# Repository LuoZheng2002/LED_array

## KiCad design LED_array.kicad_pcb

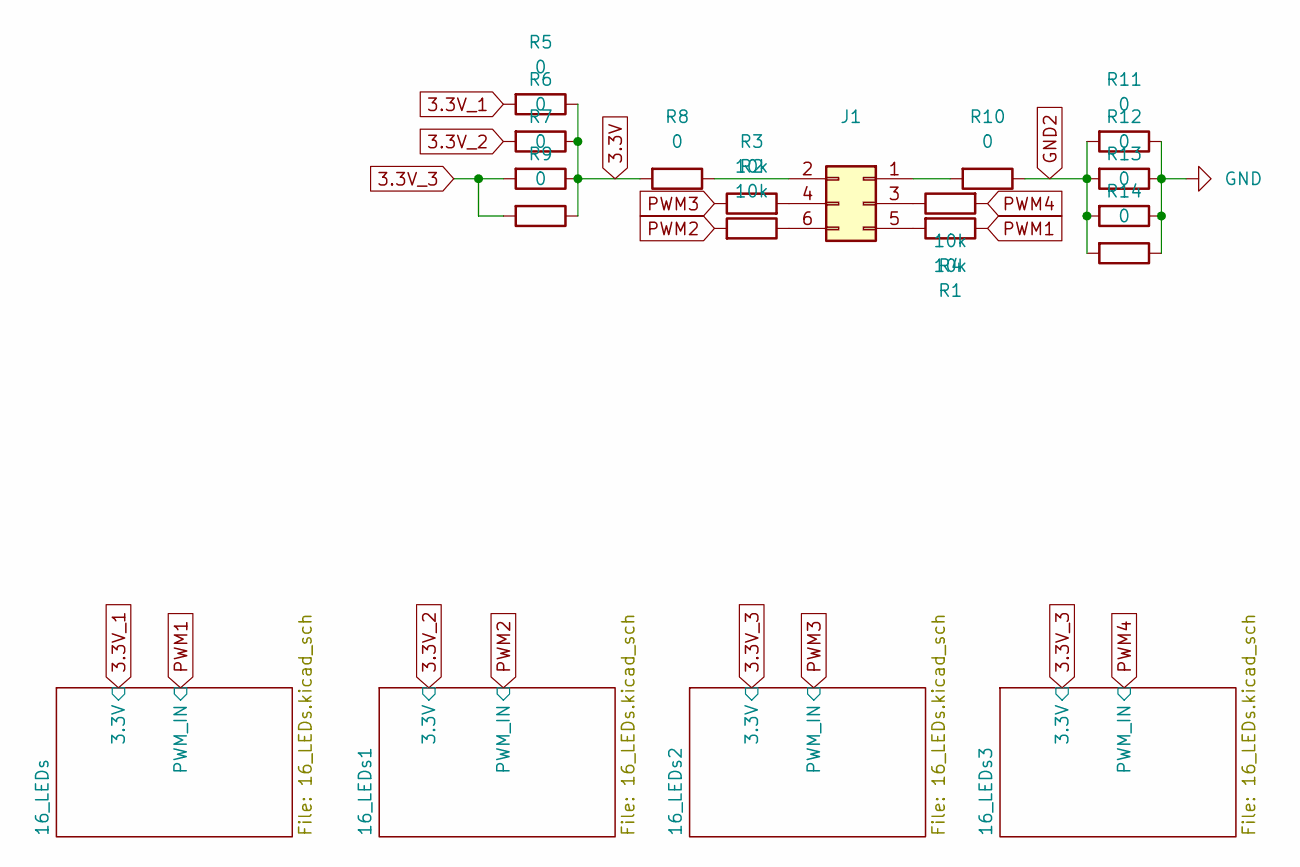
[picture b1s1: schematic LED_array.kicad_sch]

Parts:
J1: Conn_02x03_Odd_Even; PinSocket_2x03_P2.54mm_Vertical
R1, R2, R3, R4: 10k; R_Axial_DIN0207_L6.3mm_D2.5mm_P7.62mm_Horizontal
R5, R6, R11: 0; R_Axial_DIN0204_L3.6mm_D1.6mm_P5.08mm_Horizontal
R7, R8, R9, R12: 0; R_Axial_DIN0204_L3.6mm_D1.6mm_P7.62mm_Horizontal
R10, R13, R14: 0; my10.16mm_resistor

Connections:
3.3V: R5.1, R6.1, R7.1, R8.2, R9.1
3.3V_1: R5.2; also elsewhere on the board
3.3V_2: R6.2; also elsewhere on the board
3.3V_3: R7.2, R9.2; also elsewhere on the board
GND: R11.1, R12.1, R13.1, R14.1; also elsewhere on the board
GND2: R10.1, R11.2, R12.2, R13.2, R14.2
unnamed: J1.1, R10.2
unnamed: J1.2, R8.1
unnamed: J1.3, R4.1
unnamed: J1.4, R3.2
unnamed: J1.5, R1.2
unnamed: J1.6, R2.1
PWM1: R1.1; also elsewhere on the board
PWM2: R2.2; also elsewhere on the board
PWM3: R3.1; also elsewhere on the board
PWM4: R4.2; also elsewhere on the board

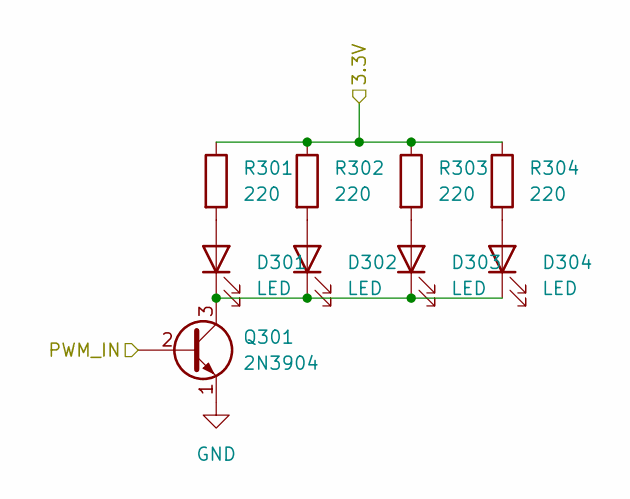
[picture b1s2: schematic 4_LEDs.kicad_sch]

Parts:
D301, D302, D303, D304: LED; LED_D5.0mm
Q301: 2N3904; TO-92_Inline
R301, R302, R303, R304: 220; R_Axial_DIN0207_L6.3mm_D2.5mm_P7.62mm_Horizontal

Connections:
3.3V_1: R301.1, R302.1, R303.1, R304.1; also elsewhere on the board
GND: Q301.1 (E); also elsewhere on the board
unnamed: D301.2 (A), R301.2
unnamed: D301.1 (K), D302.1 (K), D303.1 (K), D304.1 (K), Q301.3 (C)
unnamed: D302.2 (A), R302.2
unnamed: D303.2 (A), R303.2
unnamed: D304.2 (A), R304.2
PWM1: Q301.2 (B); also elsewhere on the board

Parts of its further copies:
D401, D402, D403, D404, D501, D502, D503, D504, D601, D602, D603, D604, D801, D802, D803, D804, D901, D902, D903, D904, D1001, D1002, D1003, D1004, D1101, D1102, D1103, D1104, D1301, D1302, D1303, D1304, D1401, D1402, D1403, D1404, D1501, D1502, D1503, D1504, D1601, D1602, D1603, D1604, D1801, D1802, D1803, D1804, D1901, D1902, D1903, D1904, D2001, D2002, D2003, D2004, D2101, D2102, D2103, D2104: LED; LED_D5.0mm
Q401, Q501, Q601, Q801, Q901, Q1001, Q1101, Q1301, Q1401, Q1501, Q1601, Q1801, Q1901, Q2001, Q2101: 2N3904; TO-92_Inline
R401, R402, R403, R404, R501, R502, R503, R504, R601, R602, R603, R604, R801, R802, R803, R804, R901, R902, R903, R904, R1001, R1002, R1003, R1004, R1101, R1102, R1103, R1104, R1301, R1302, R1303, R1304, R1401, R1402, R1403, R1404, R1501, R1502, R1503, R1504, R1601, R1602, R1603, R1604, R1801, R1802, R1803, R1804, R1901, R1902, R1903, R1904, R2001, R2002, R2003, R2004, R2101, R2102, R2103, R2104: 220; R_Axial_DIN0207_L6.3mm_D2.5mm_P7.62mm_Horizontal

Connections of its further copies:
3.3V_1: R401.1, R402.1, R403.1, R404.1, R501.1, R502.1, R503.1, R504.1, R601.1, R602.1, R603.1, R604.1; also elsewhere on the board
3.3V_2: R801.1, R802.1, R803.1, R804.1, R901.1, R902.1, R903.1, R904.1, R1001.1, R1002.1, R1003.1, R1004.1, R1101.1, R1102.1, R1103.1, R1104.1; also elsewhere on the board
3.3V_3: R1301.1, R1302.1, R1303.1, R1304.1, R1401.1, R1402.1, R1403.1, R1404.1, R1501.1, R1502.1, R1503.1, R1504.1, R1601.1, R1602.1, R1603.1, R1604.1, R1801.1, R1802.1, R1803.1, R1804.1, R1901.1, R1902.1, R1903.1, R1904.1, R2001.1, R2002.1, R2003.1, R2004.1, R2101.1, R2102.1, R2103.1, R2104.1; also elsewhere on the board
GND: Q401.1 (E), Q501.1 (E), Q601.1 (E), Q801.1 (E), Q901.1 (E), Q1001.1 (E), Q1101.1 (E), Q1301.1 (E), Q1401.1 (E), Q1501.1 (E), Q1601.1 (E), Q1801.1 (E), Q1901.1 (E), Q2001.1 (E), Q2101.1 (E); also elsewhere on the board
unnamed: D401.2 (A), R401.2
unnamed: D401.1 (K), D402.1 (K), D403.1 (K), D404.1 (K), Q401.3 (C)
unnamed: D402.2 (A), R402.2
unnamed: D403.2 (A), R403.2
unnamed: D404.2 (A), R404.2
unnamed: D501.2 (A), R501.2
unnamed: D501.1 (K), D502.1 (K), D503.1 (K), D504.1 (K), Q501.3 (C)
unnamed: D502.2 (A), R502.2
unnamed: D503.2 (A), R503.2
unnamed: D504.2 (A), R504.2
unnamed: D601.2 (A), R601.2
unnamed: D601.1 (K), D602.1 (K), D603.1 (K), D604.1 (K), Q601.3 (C)
unnamed: D602.2 (A), R602.2
unnamed: D603.2 (A), R603.2
unnamed: D604.2 (A), R604.2
unnamed: D801.2 (A), R801.2
unnamed: D801.1 (K), D802.1 (K), D803.1 (K), D804.1 (K), Q801.3 (C)
unnamed: D802.2 (A), R802.2
unnamed: D803.2 (A), R803.2
unnamed: D804.2 (A), R804.2
unnamed: D901.2 (A), R901.2
unnamed: D901.1 (K), D902.1 (K), D903.1 (K), D904.1 (K), Q901.3 (C)
unnamed: D902.2 (A), R902.2
unnamed: D903.2 (A), R903.2
unnamed: D904.2 (A), R904.2
unnamed: D1001.2 (A), R1001.2
unnamed: D1001.1 (K), D1002.1 (K), D1003.1 (K), D1004.1 (K), Q1001.3 (C)
unnamed: D1002.2 (A), R1002.2
unnamed: D1003.2 (A), R1003.2
unnamed: D1004.2 (A), R1004.2
unnamed: D1101.2 (A), R1101.2
unnamed: D1101.1 (K), D1102.1 (K), D1103.1 (K), D1104.1 (K), Q1101.3 (C)
unnamed: D1102.2 (A), R1102.2
unnamed: D1103.2 (A), R1103.2
unnamed: D1104.2 (A), R1104.2
unnamed: D1301.2 (A), R1301.2
unnamed: D1301.1 (K), D1302.1 (K), D1303.1 (K), D1304.1 (K), Q1301.3 (C)
unnamed: D1302.2 (A), R1302.2
unnamed: D1303.2 (A), R1303.2
unnamed: D1304.2 (A), R1304.2
unnamed: D1401.2 (A), R1401.2
unnamed: D1401.1 (K), D1402.1 (K), D1403.1 (K), D1404.1 (K), Q1401.3 (C)
unnamed: D1402.2 (A), R1402.2
unnamed: D1403.2 (A), R1403.2
unnamed: D1404.2 (A), R1404.2
unnamed: D1501.2 (A), R1501.2
unnamed: D1501.1 (K), D1502.1 (K), D1503.1 (K), D1504.1 (K), Q1501.3 (C)
unnamed: D1502.2 (A), R1502.2
unnamed: D1503.2 (A), R1503.2
unnamed: D1504.2 (A), R1504.2
unnamed: D1601.2 (A), R1601.2
unnamed: D1601.1 (K), D1602.1 (K), D1603.1 (K), D1604.1 (K), Q1601.3 (C)
unnamed: D1602.2 (A), R1602.2
unnamed: D1603.2 (A), R1603.2
unnamed: D1604.2 (A), R1604.2
unnamed: D1801.2 (A), R1801.2
unnamed: D1801.1 (K), D1802.1 (K), D1803.1 (K), D1804.1 (K), Q1801.3 (C)
unnamed: D1802.2 (A), R1802.2
unnamed: D1803.2 (A), R1803.2
unnamed: D1804.2 (A), R1804.2
unnamed: D1901.2 (A), R1901.2
unnamed: D1901.1 (K), D1902.1 (K), D1903.1 (K), D1904.1 (K), Q1901.3 (C)
unnamed: D1902.2 (A), R1902.2
unnamed: D1903.2 (A), R1903.2
unnamed: D1904.2 (A), R1904.2
unnamed: D2001.2 (A), R2001.2
unnamed: D2001.1 (K), D2002.1 (K), D2003.1 (K), D2004.1 (K), Q2001.3 (C)
unnamed: D2002.2 (A), R2002.2
unnamed: D2003.2 (A), R2003.2
unnamed: D2004.2 (A), R2004.2
unnamed: D2101.2 (A), R2101.2
unnamed: D2101.1 (K), D2102.1 (K), D2103.1 (K), D2104.1 (K), Q2101.3 (C)
unnamed: D2102.2 (A), R2102.2
unnamed: D2103.2 (A), R2103.2
unnamed: D2104.2 (A), R2104.2
PWM1: Q401.2 (B), Q501.2 (B), Q601.2 (B); also elsewhere on the board
PWM2: Q801.2 (B), Q901.2 (B), Q1001.2 (B), Q1101.2 (B); also elsewhere on the board
PWM3: Q1301.2 (B), Q1401.2 (B), Q1501.2 (B), Q1601.2 (B); also elsewhere on the board
PWM4: Q1801.2 (B), Q1901.2 (B), Q2001.2 (B), Q2101.2 (B); also elsewhere on the board

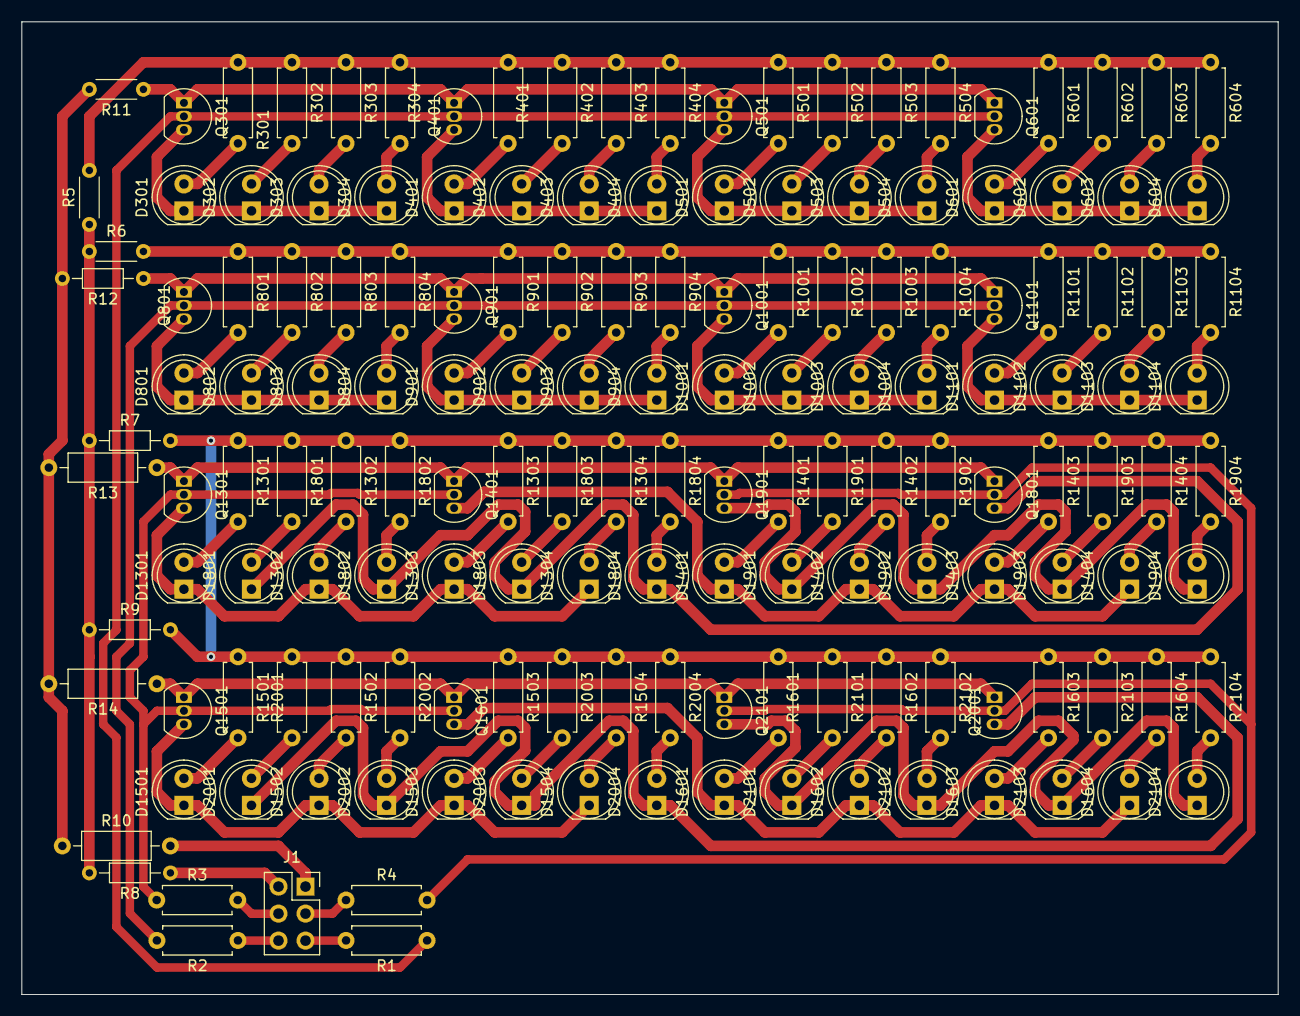
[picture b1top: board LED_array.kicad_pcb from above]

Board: 2 copper layers, 118.1 x 91.4 mm, 159 parts (0 on the bottom side), 96 nets.

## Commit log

2024-01-22 checkpoint
